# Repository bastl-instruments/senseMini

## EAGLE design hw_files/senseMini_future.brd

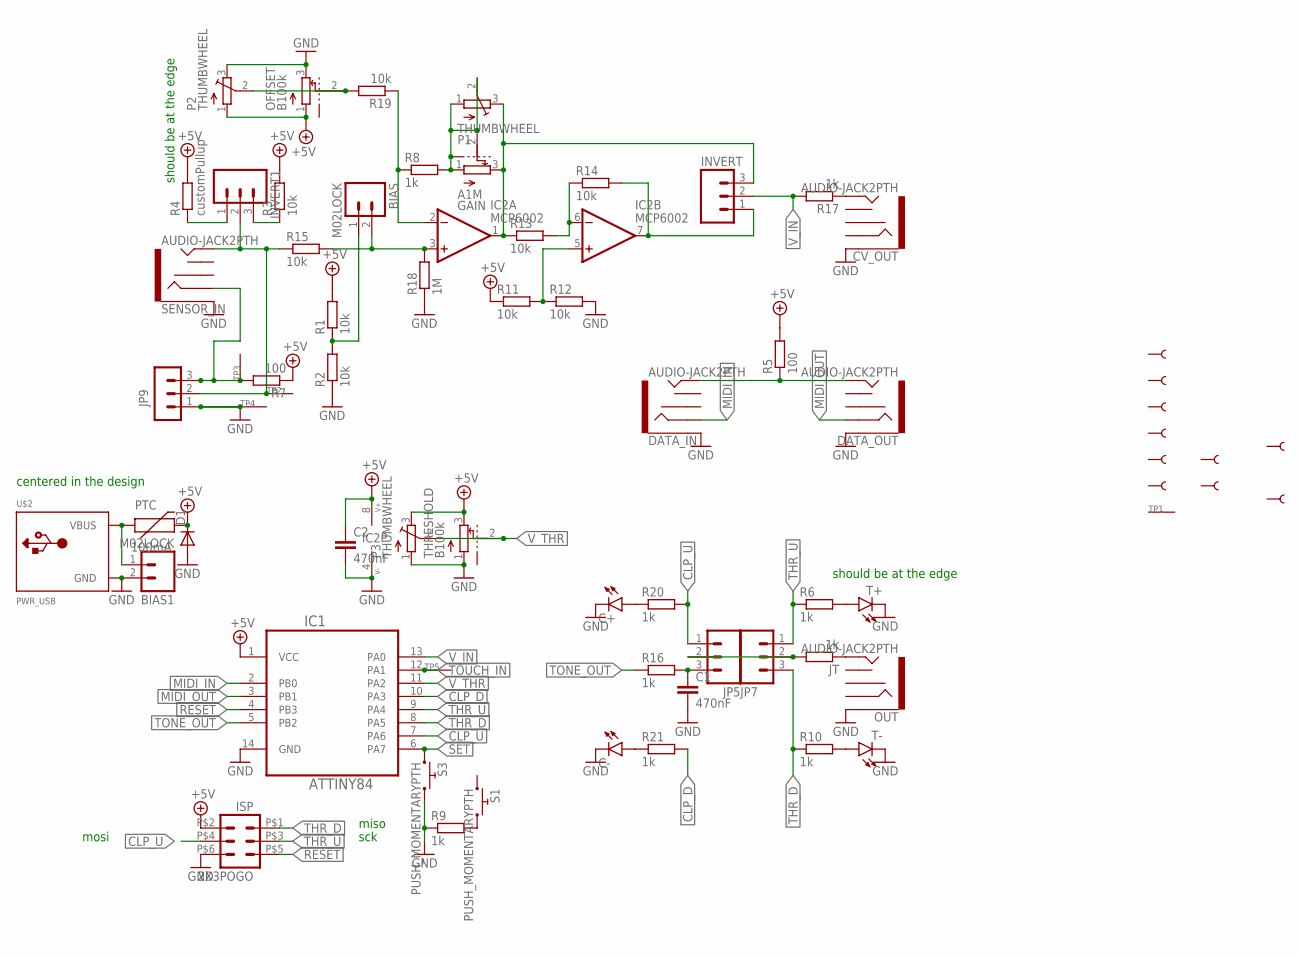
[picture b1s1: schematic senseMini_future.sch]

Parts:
BIAS, BIAS1: M02LOCK; 1X02_LOCK
C1, C2: 470nF; C_C050-024X044
C+: LED_THT; LEDSMALLHOLES
C-: LED_THT; LEDSMALLHOLES
CV_OUT: AUDIO-JACK2PTH; AUDIO-JACK
D1: DIODE-D-5; D-5
DATA_IN: AUDIO-JACK2PTH; AUDIO-JACK
DATA_OUT: AUDIO-JACK2PTH; AUDIO-JACK
GAIN: A1M; POT_ALPHA
IC1: ATTINY84; DIP254P762X533-14
IC2: MCP6002; DIL08
INVERT, INVERT1: M03LOCK; 1X03_LOCK
ISP: 2X3POGO; 2X3_POGO
JP5, JP7: M03LOCK; 1X03_LOCK
JP9: 1X3_FEMALE; HEADER_1X3_FEMALE
JT: 1k; RCL_0204/5
OFFSET: B100k; POT_ALPHA
OUT: AUDIO-JACK2PTH; AUDIO-JACK
P1, P2, P3: THUMBWHEEL
PTC: 100mA; PTC_THT
R1, R2, R3, R11, R12, R13, R14, R15, R19: 10k; RCL_0204/5
R4: customPullup; RCL_0204/5
R5, R7: 100; RCL_0204/5
R6, R8, R9, R10, R16, R17, R20, R21: 1k; RCL_0204/5
R18: 1M; RCL_0204/5
S1, S3: PUSH_MOMENTARYPTH; TACTILE-PTH
SENSOR_IN: AUDIO-JACK2PTH; AUDIO-JACK
T+: LED_THT; LEDSMALLHOLES
T-: LED_THT; LEDSMALLHOLES
THRESHOLD: B100k; POT_ALPHA
TP1: SEWTAP-2.0IN; SEWINGTAP_2.0
TP2, TP3, TP4, TP5: SEWTAP0.5IN; SEWINGTAP_0.5
U$2: PWR_USB; USBMICRO
U$3, U$4, U$9, U$10, U$11, U$12: SEWTAP2; PETAL-LONG-2
U$5, U$6, U$7, U$8: SEWTAP6; PETAL-SMALL-2SIDE

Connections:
+5V: C2.1, D1.C, IC1.1 (VCC), IC2.8 (V+), ISP.P$2 (2), OFFSET.1, P2.1 (A), P3.3 (E), PTC.P$2 (2), R1.2, R3.2, R4.2, R5.2, R7.1, R11.1, THRESHOLD.3
CLP_D: IC1.10 (PA3), R21.2
CLP_U: IC1.7 (PA6), ISP.P$4 (4), JP5.1, R20.2
GND: BIAS1.2, C1.2, C2.2, C+.K (C), C-.K (C), CV_OUT.SLEEVE, D1.A, DATA_IN.SLEEVE, DATA_OUT.SLEEVE, IC1.14 (GND), IC2.4 (V-), ISP.P$6 (6), JP9.1, OFFSET.3, OUT.SLEEVE, P2.3 (E), P3.1 (A), R2.1, R9.1, R12.2, R18.1, S3.3 (2), S3.4 (2), SENSOR_IN.SLEEVE, T+.K (C), T-.K (C), THRESHOLD.1, TP4.TAP, U$2.GND, U$2.GND1 (GND)
MIDI_IN: DATA_IN.RING, IC1.2 (PB0)
MIDI_OUT: DATA_OUT.RING, IC1.3 (PB1)
unnamed: BIAS1.1, PTC.P$1 (1), U$2.V+ (VBUS), U$2.V+1 (VBUS)
unnamed: INVERT1.1, R4.1
unnamed: BIAS.1, R1.1, R2.2
unnamed: INVERT1.3, R3.1
unnamed: C+.A, R20.1
unnamed: DATA_IN.TIP, DATA_OUT.TIP, R5.1
unnamed: JP9.3, R7.2, SENSOR_IN.RING, TP3.TAP
unnamed: INVERT1.2, JP9.2, R15.1, SENSOR_IN.TIP, TP2.TAP
unnamed: R6.2, T+.A
unnamed: JP5.2, JP7.2, JT.2
unnamed: GAIN.3, IC2.1 (OUT), INVERT.3, P1.3 (E), R13.1
unnamed: C1.1, JP5.3, R16.2
unnamed: R10.2, T-.A
unnamed: GAIN.1, GAIN.2, GAIN.P$1, GAIN.P$2, P1.1 (A), P1.2 (S), R8.2
unnamed: BIAS.2, IC2.3 (+IN), R15.2, R18.2
unnamed: R9.2, S1.3 (2), S1.4 (2)
unnamed: C-.A, R21.1
unnamed: IC2.5 (+IN), R11.2, R12.1
unnamed: IC2.6 (-IN), R13.2, R14.1
unnamed: IC2.7 (OUT), INVERT.1, R14.2
unnamed: JT.1, OUT.TIP
unnamed: CV_OUT.TIP, R17.1
unnamed: IC2.2 (-IN), R8.1, R19.1
unnamed: OFFSET.2, P2.2 (S), R19.2
RESET: IC1.4 (PB3), ISP.P$5 (5)
SET: IC1.6 (PA7), S3.1, S3.2 (1)
THR_D: IC1.8 (PA5), ISP.P$1 (1), JP7.3, R10.1
THR_U: IC1.9 (PA4), ISP.P$3 (3), JP7.1, R6.1
TONE_OUT: IC1.5 (PB2), R16.1
TOUCH_IN: IC1.12 (PA1), TP5.TAP
V_IN: IC1.13 (PA0), INVERT.2, R17.2
V_THR: IC1.11 (PA2), P3.2 (S), THRESHOLD.2

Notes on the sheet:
mosi
miso
sck
should be at the edge
centered in the design

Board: 2 copper layers, 70 parts (1 on the bottom side), 38 nets, no tracks yet.

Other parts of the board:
U$1: 3MM_HOLE

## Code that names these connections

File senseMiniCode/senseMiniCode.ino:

/*
   license: CC-BY-SA
   senseMini by Václav Peloušek http://bastl-instruments.com
   sensor calibration module
   the code analyses sensor voltage and threshold voltage and converts them into:
    -LED indictaion
    -sound generation
    -midi information

   open for further ideas
   made for pifcamp 2018 http://pif.camp

   full documentation at:https://github.com/bastl-instruments/senseMini
*/
#include <SoftwareSerial.h>
#include <MIDI.h>
#include <EEPROM.h>

#define ANALOG_INPUT 0
#define TOUCH_INPUT 1
#define THRESHOLD 2
#define CLP_D 3
#define CLP_U 6
#define THR_U 4
#define THR_D 5
#define BUTTON_PIN 7
#define MIDI_IN 10
#define MIDI_OUT 9
#define TONE_OUT 8

const char PROGMEM sinetable[128] = {
  0, 0, 0, 0, 1, 1, 1, 2, 2, 3, 4, 5, 5, 6, 7, 9, 10, 11, 12, 14, 15, 17, 18, 20, 21, 23, 25, 27, 29, 31, 33, 35, 37, 40, 42, 44, 47, 49, 52, 54, 57, 59, 62, 65, 67, 70, 73, 76, 79, 82, 85, 88, 90, 93, 97, 100, 103, 106, 109, 112, 115, 118, 121, 124,
  128, 131, 134, 137, 140, 143, 146, 149, 152, 155, 158, 162, 165, 167, 170, 173, 176, 179, 182, 185, 188, 190, 193, 196, 198, 201, 203, 206, 208, 211, 213, 215, 218, 220, 222, 224, 226, 228, 230, 232, 234, 235, 237, 238, 240, 241, 243, 244, 245, 246, 248, 249, 250, 250, 251, 252, 253, 253, 254, 254, 254, 255, 255, 255,
};

SoftwareSerial softSerial(MIDI_IN, MIDI_OUT);

struct MySettings : public midi::DefaultSettings
{
  static const unsigned SysExMaxSize = 1; // Accept SysEx messages up to 1024 bytes long.
};

MIDI_CREATE_CUSTOM_INSTANCE(SoftwareSerial, softSerial, midiA, MySettings);


bool buttonState = false;

#define NUMBER_OF_SOUND_MODES 4
#define FREQUENCY 0
#define TIMBRE 1
#define AMPLITUDE 2

uint8_t timbre = 0;
uint8_t amplitude = 255;
uint8_t soundMode = 0;

#define MIDI_NOTE 56
#define MIDI_CC 30
#define MIDI_CHANNEL 1
#define LEARNING_CC 120
#define LEARNING_CHANNEL 16
#define PRESCALE _BV(CS10)

uint32_t _timeCounter, _time;
bool thresholdState = false;
bool otherIsLearning = false;
int analogValue, lastAnalogValue;
int threshold;
unsigned int _phase, _phase2;
uint8_t sample;
unsigned int frequency = 500;
bool flop;
unsigned char wavetable[256];


void handleNoteOn(byte channel, byte pitch, byte velocity)
{
  //if (channel == MIDI_CHANNEL && !buttonState)
  midiA.sendNoteOn(pitch + 1, velocity, MIDI_CHANNEL);
}

void handleNoteOff(byte channel, byte pitch, byte velocity)
{
  //if (channel == MIDI_CHANNEL && !buttonState)
  midiA.sendNoteOff(pitch + 1, velocity, MIDI_CHANNEL);
}

void handleControlChange(byte channel, byte number, byte value)
{
  //if (channel == MIDI_CHANNEL && !buttonState)
  midiA.sendControlChange(number + 1, value, MIDI_CHANNEL);

  if (channel == LEARNING_CHANNEL && number == LEARNING_CC) otherIsLearning = value >> 6;
}

void setTheTimers() {
  TCCR0A = 2 << COM0A0 | 2 << COM0B0 | 3 << WGM00;
  TCCR0B = 0 << WGM02 | 1 << CS00;

  bitWrite(TCCR0B, CS00, 1);
  bitWrite(TCCR0B, CS01, 0);
  bitWrite(TCCR0B, CS02, 0);

  TCCR1A = 0;
  TCCR1B = 0;
  TCCR1B |= (1 << WGM12); // configure timer1 for CTC mode
  //TIMSK1 |= (1 << OCIE1A); // enable the CTC interrupt
  bitWrite( TIMSK1,OCIE1A,soundMode!=3);
  sei(); // enable global interrupts
  OCR1A = 255; // Should return frequency ~1000hz
  TCCR1B |= PRESCALE;
}
#define SOUND_MODE_BYTE 7
void setup() {

  //set all the pins
  pinMode(ANALOG_INPUT, INPUT);
  pinMode(TOUCH_INPUT, INPUT);
  pinMode(THRESHOLD, INPUT);

  pinMode(CLP_D, OUTPUT);
  pinMode(CLP_U, OUTPUT);
  pinMode(THR_U, OUTPUT);
  pinMode(THR_D, OUTPUT);

  pinMode(BUTTON_PIN, INPUT_PULLUP);

  pinMode(MIDI_IN, INPUT);
  pinMode(MIDI_OUT, OUTPUT);
  pinMode(TONE_OUT, OUTPUT);
  
  soundMode=EEPROM.read(SOUND_MODE_BYTE);
  soundMode%=NUMBER_OF_SOUND_MODES;
  
  sineWave(); //fill the wavetable
  setTheTimers(); //some black magic to make the audio generation
  
  //init the midi
  midiA.begin(MIDI_CHANNEL_OMNI);
  midiA.turnThruOff();
  midiA.setHandleNoteOn(handleNoteOn);
  midiA.setHandleNoteOff(handleNoteOff);
  midiA.setHandleControlChange(handleControlChange);
  

}

void sineWave() {                                       //too costly to calculate on the fly, so it reads from the sine table. We use 128 values, then mirror them to get the whole cycle
  for (int i = 0; i < 128; ++i) {
    wavetable[i] = pgm_read_byte_near(sinetable + i);
  }
  wavetable[128] = 255;
  for (int i = 129; i < 256; ++i) {
    wavetable[i] = wavetable[256 - i] ;
  }
}
const uint8_t ledNumber[4]={CLP_U,THR_U,THR_D,CLP_D};
void loop() {

  midiA.read();

  bool newState = !digitalRead(BUTTON_PIN);
  if (!buttonState && newState) { //button just pressed
    soundMode++;
    soundMode = soundMode % NUMBER_OF_SOUND_MODES;
    EEPROM.write(SOUND_MODE_BYTE,soundMode);
    if(soundMode==3){
     // cli();
     
        bitWrite( TIMSK1,OCIE1A,0);
    }
    else  bitWrite( TIMSK1,OCIE1A,1);//sei();
    // midiA.sendControlChange(LEARNING_CC, 127, LEARNING_CHANNEL);
  }
  if (buttonState && !newState) {
    //  midiA.sendControlChange(LEARNING_CC, 0, LEARNING_CHANNEL);
  }
  buttonState = newState;

  switch (soundMode) {

    case FREQUENCY:
      frequency = (analogValue << 2) + 50;
      timbre = 0;
      amplitude = 255;
      break;

    case TIMBRE:
      timbre = constrain(analogValue >> 2, 1, 255);
      amplitude = 255;
      break;

    case AMPLITUDE:
      amplitude = analogValue >> 2;
      timbre = 128;

      break;

  }

  analogValue = analogRead(ANALOG_INPUT);



  if (_timeCounter - _time > 400) {
    if (1) { //!otherIsLearning) {
      if (analogValue >> 3 != lastAnalogValue) midiA.sendControlChange(MIDI_CC, analogValue >> 3, MIDI_CHANNEL);
      _time = _timeCounter;
      lastAnalogValue = analogValue >> 3;
    }
  }

  threshold = analogRead(THRESHOLD);

  bool newThresholdState = analogValue > threshold;

  if (newThresholdState && !thresholdState) {
    //if (!otherIsLearning)
    midiA.sendNoteOn(MIDI_NOTE, constrain(threshold >> 3, 1, 127), MIDI_CHANNEL);
  }
  if (!newThresholdState && thresholdState) {
    //if (!otherIsLearning)
    midiA.sendNoteOff(MIDI_NOTE, constrain(threshold >> 3, 1, 127), MIDI_CHANNEL);
  }
  thresholdState = newThresholdState;

  if (buttonState) {
    for(uint8_t i;i<4;i++){
      digitalWrite(ledNumber[i],LOW);
    }
    digitalWrite(ledNumber[soundMode],HIGH);
  }
  else {
    if (analogValue > 1000) digitalWrite(CLP_U, HIGH);
    else digitalWrite(CLP_U, LOW);

    if (analogValue < 23) digitalWrite(CLP_D, HIGH);
    else digitalWrite(CLP_D, LOW);

    if (thresholdState) {
      digitalWrite(THR_U, HIGH);
      digitalWrite(THR_D, LOW);
    }
    else {
      digitalWrite(THR_U, LOW);
      digitalWrite(THR_D, HIGH);
    }
  }
}

ISR(TIM1_COMPA_vect)  // render the oscillators in the interupt
{

  OCR0A = sample;
  _phase += frequency;
  _phase2 += frequency;
  _phase2 += frequency;
  uint8_t _phs = (_phase + (timbre * wavetable[_phase2 >> 8])) >> 8;
  sample = (amplitude * (wavetable[_phs] )) >> 8;

  _timeCounter++; //time reference for the main loop

}

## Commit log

2018-08-09 initial commit - schematics & code & manual
2018-08-09 added manual + hw files + use cases
2018-08-09 added git link
2018-08-10 ADDED SKETCH FOR FUTURE DESIGN

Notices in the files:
parts and their libraries:
SparkFun-Connectors: Licensing: Creative Commons ShareAlike 4.0 International - https://creativecommons.org/licenses/by-sa/4.0
